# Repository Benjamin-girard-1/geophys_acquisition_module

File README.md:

# Geophysical Acquisition Module

Hardware, embedded firmware, protocol, and host-side software for a modular
geophysical data-acquisition system.

Version 2 uses an ESP32-S3 DevKit as its immutable compute platform and a custom
carrier PCB organized by hardware revision. The current hardware design includes
an AD7779 ADC, an LSM6DSV IMU, MAX-M10S GNSS, SD storage shared with a USB2641,
74HC/HCT595 GPIO expansion, and removable analog acquisition cards.

## Current status

The Version 2 firmware builds with ESP-IDF 5.5. Board safe-state and power
control, portable GPIO/SPI/UART, calibrated analog-input, and ROM-backed CRC
mechanisms, the 74HC/HCT595 driver, bounded analog-card ID measurement, and the
AD7779 register, lifecycle, channel/gain, fixed output-rate, signed sample
decoding, and conversion-frame validation foundations are implemented.
The acquisition task, SD recording owner, and recording controller now provide
the first end-to-end recording implementation and UART live-stream path, while
the remaining protocol inventory is still in progress. Hardware verification
is being completed incrementally.
The authoritative protocol defines fixed 64-byte command messages and portable
512-byte ADC data blocks shared by live capture and SD recording. Fixed command
framing, incremental stream recovery, CRC validation, and the
`HELLO`/`DEVICE_INFO` plus `DEVICE_GET_CONFIG`/`DEVICE_SET_CONFIG` UART slices
are implemented and verified on Rev-1 hardware. Live start/stop, complete
512-byte UART data delivery, the five SD-recording commands,
the portable `\DAT` encoder/decoder, fixed recording-buffer pool, and FatFs
writer are implemented; a clean Rev-1 build mounts and catalogs the SD card,
and now creates, syncs, closes, catalogs, and deletes ADC data files on Rev-1
hardware. A temporary test-only `0xf000` command can read closed recording
files in 38-byte UART chunks; it is implemented in the firmware and host codec
and was used to retrieve and CRC-validate a stored 512-byte block. A two-second
protocol probe produced and cleanly closed 404 fixed
512-byte records while configuration commands remained responsive. The probe
also exposed and led to correction of acquisition-task starvation and a
FreeRTOS queue-set accounting error that rebooted the device after several SD
records. Comparison with the working V1 driver identified and corrected
premature post-reset polling failure, missing reference-output power, missing
SPI software reset, and missing filter synchronization. The earlier all-zero
ADC response was a bench power issue: the main +5 V supply was absent, so 3V3A
was unavailable. Restoring +5 V allowed AD7779 initialization and recording to
proceed. The two expendable recordings that filled the card were enumerated
and deleted through the recording protocol, leaving an empty catalog. A
subsequent fresh probe recorded, downloaded, validated, and deleted ten
512-byte records. All record framing and CRCs passed. That early capture
contained 80 startup conversions near the AD7779 reset rate followed by a
sequence gap. The cause was an ESP-IDF side effect that enabled the DRDY pin
while its handler was attached, before ADC synchronization and SRC settling
completed. The platform attach operation now restores the pin to disabled and
the application enables it explicitly after `ad7779_start()`. A fresh 1 kSPS
probe then produced 25 status-OK records with no missing conversions. The
acquisition hot path now reserves SPI2 and its DMA resources once and launches
one hardware-CS-framed, prepared 32-byte transfer for each DRDY event. A
dedicated core-1 capture task advances the two-buffer DMA pipeline and
copies completed frames into a 256-frame ring; CRC validation, DAT construction,
and storage handoff run independently on core 0. The hardware-tested storage
baseline used two 2 MiB PSRAM buffers: acquisition filled one continuously
while the storage task wrote the other through a 32 KiB internal SDMMC staging
window. A 50-second four-channel 8 kSPS probe crossed both 2 MiB boundaries
without stopping acquisition or losing a conversion. The current
noise-diagnostic implementation expands this to three 2 MiB buffers. Two
buffers accumulate one conversion-count-scheduled batch, while the third keeps
acquisition running during the grouped SD write and single filesystem sync.
Stored-record CRC generation is also deferred to that same SD activity window,
removing the 508-byte PSRAM reread from each 40-conversion record boundary;
live-stream records continue to receive their CRC immediately.
For four channels, batches occur every five minutes at 1 kSPS, two minutes at
2 kSPS, one minute at 4 kSPS, and 30 seconds at 8 kSPS. A Rev-1 8 kSPS test
recorded 35,333 records, crossed five scheduled 6,000-record boundaries with
status-OK and sequence-contiguous records on both sides, and cleanly flushed
the final partial batch. Magnetic-noise comparison remains open. The four-bit
SDMMC bus runs at its verified 40 MHz
high-speed setting; every scheduled batch and the recording close are
synchronized to the filesystem. The SD volume uses FAT32
with 32 KiB clusters so FatFs can issue 32 KiB multi-sector writes instead of
splitting at the former 4 KiB cluster boundaries. A two-second
channels-0–3 probe at 16 kSPS retained all 32,840 consecutive conversions at
625 x 100 ns spacing, with zero sequence gaps and an effective 16,000.04
conversions/s. DAT production waits for eight consecutive ADC frames to pass
CRC; the final short 16 kSPS probe and one-second 1 kSPS control contained only
status-OK records with zero missing conversions. A later 237-second capture retained
every conversion but exposed 72 isolated CRC-marked frame-phase errors at the
fixed 20 MHz SPI clock. Because AD7779 SDO output-valid timing does not support
that read rate in the worst case, lower clocks were tested. Fixed 8 MHz was
clean at 1 kSPS but could not complete valid frames at 16 kSPS with the current
DRDY-to-DMA launch latency. Fixed 10 MHz and 12 MHz produced records but still
lost conversions. A longer fixed-16-MHz capture then lost 23,438 conversions
and contained 243 CRC-marked frame errors in 93.9 seconds. The current
diagnostic build returned to fixed 20 MHz and lets the SPI peripheral assert
and release CS around every DMA burst. A two-second channels-0–3 16 kSPS probe
retained all 32,480 conversions with zero gaps, but two isolated phase errors
remained. Per-frame CS is therefore fast enough but does not by itself correct
the 20 MHz SDO integrity failure.
Configuration currently applies the stopped-device ADC rate, channel mask,
per-channel gains, and three sequenced acquisition rails; +5 VA and IMU remain
status-only. The +18 V rail is owned by a dedicated stopped-acquisition
magnetic SET/RESET command that returns the rail and pulse outputs to their
safe state. The Python host now has streaming
start/stop codecs, an incremental mixed command/data parser, named-reply
matching during live data, byte-exact validated capture, continuity counters,
and a desktop GUI with manual USB/COM selection, recording management, and a
separate live-plot tab. Its Config tab now reads device status and applies the
stopped-device ADC rate, four-channel slot selection, per-channel gains, and
acquisition-rail requests.
It also separates device-reported power-rail states from editable manual rail
requests and provides a detected-card-gated SET/RESET pulse control.
The GUI connection and recording catalog were exercised against Rev-1,
including creation, stop/close, catalog, and deletion of a GUI test recording.
A reversible channels-0–3 configuration update also passed on Rev-1. Firmware
live delivery was then exercised at 921600 baud with eight channels at 1 kSPS
and with four-channel decimation-by-5: start/stop replies and all received block
CRCs passed, streaming continued while an SD recording was opened, and
reconnect succeeded after the five-second session timeout. The live blocks
still expose the known ADC critical status and startup sequence loss, so
scientific-data validation remains open.

On 2026-09-29, the currently inserted SD card mounted and its six-file catalog
remained readable, but a new recording faulted on its first 512-byte write.
The failure reproduced with the untouched default `0xFF` configuration and
with channels 0–3 (`0x0F`), including after a device reset, while an `0x0F`
live stream continued to deliver validly framed blocks. Querying the retained
recording failure through `RECORDING_STOP` returned `0x0a` (`storage full`).
This isolates the failure from host configuration and four-channel
acquisition; space must be freed or the FAT32 volume repaired before recording.

The first Bluetooth Low Energy slice is also implemented. When enabled, the
ESP32-S3 advertises `Geophys Acquisition`, accepts one BLE central, and answers
`HELLO` with the existing `DEVICE_INFO` message. The desktop host can scan,
connect, and display that identity; other commands and live data remain
disabled on Bluetooth for now. Rev-1 bench verification passed BLE discovery
and `HELLO` while a USB command session remained active. The current
2026-10-03 field-test build intentionally sets `APP_BLUETOOTH_ENABLED` to zero
in `version_2/firmware/app/app.c`. This radio-silent diagnostic configuration
removed the measured 60–70 ms BLE advertising disturbance and preserves the
implemented BLE code for later re-enablement.

The same field-test build enables unattended SD recording. With no valid saved
configuration, its defaults are 8 kSPS, channels 0–3 enabled, gain x8 on
channels 0–2, and gain x1 on channel 3; channels 4–7 are disabled. A successful
wired `DEVICE_SET_CONFIG` commits the sample rate, channel mask, and all eight
gains to the ESP32's wear-levelled internal flash. These settings are restored
after reset or power loss; live rail/status fields are not persistent. The
firmware waits five seconds after application initialization, then creates the
first free name from `field000` through `field254` and starts acquisition with
the restored settings. Holding the ESP32-S3 DevKitC BOOT button for three
seconds stops the ADC, drains the PSRAM buffers, syncs the file, and closes it.
A hard power-off cannot run that cleanup: after holding BOOT, wait for the
close to finish before switching the battery off. The RESET button remains an
immediate reset and must not be used to stop a recording.

New SD recordings reserve a self-contained 32 KiB header region. Its first
4096 bytes are printable JSON containing the recording name, device and
firmware/hardware identity, card types, channel mask, gain for every channel,
sample rate, power state, channel mapping, and a link to the project tools.
The rest reserves 896 fixed 32-byte UTC/orientation checkpoints; they are
currently zero placeholders because GNSS is not installed and the IMU path is
not yet implemented. ADC DAT blocks begin at byte 32768. The JSON descriptor
passed native/Python tests and a Rev-1 readback after the 2026-10-07 flash:
`field023` had a CRC-valid, printable JSON descriptor with the configured
per-channel gains and a CRC-valid first `\DAT` block at byte 32768. The firmware
now keeps unattended recording stopped after a wired `RECORDING_STOP`, matching
the BOOT-button stop behavior. A short `field025` check confirmed that the board
stayed idle and the closed file could be read. Long-duration timing verification
remains open.

The complete wire contract is
[shared/protocol/protocol.md](shared/protocol/protocol.md). It is the sole
authority for framing, identifiers, results, command payloads, and ADC data
blocks.

See [ARCHITECTURE.md](ARCHITECTURE.md) for module responsibilities, dependency
rules, initialization order, and the detailed implementation-status table.
Milestone-1 execution and verification are tracked in
[version_2/docs/firmware_implementation_checklist.md](version_2/docs/firmware_implementation_checklist.md).

## Repository layout

```text
.
├── ARCHITECTURE.md              Firmware architecture and dependency rules
├── shared/
│   ├── kicad-libraries/         Shared KiCad symbols and footprints
│   ├── protocol/                Firmware/host wire-protocol specification
│   ├── third_party/             Pinned external dependencies
│   └── tools/                   Repository-wide development utilities
├── version_1/                   Earlier product generation
└── version_2/
    ├── docs/                    Datasheets and documentation
    ├── firmware/
    │   ├── common/              Portable types shared across firmware layers
    │   ├── main/                ESP-IDF entry point and composition root
    │   ├── app/                 Product behavior and FreeRTOS tasks
    │   ├── boards/              Custom carrier-board integration by revision
    │   ├── analog_cards/        Removable analog-card integration
    │   ├── drivers/             Portable component-specific drivers
    │   ├── data_format/         Portable serialized acquisition records
    │   ├── protocol/            Firmware framing and message encoding
    │   ├── transports/          UART, USB, and future byte transports
    │   ├── platform/
    │   │   └── esp32s3_devkit/  Immutable DevKit and ESP-IDF integration
    │   └── cmake/               Shared build helpers when required
    ├── hardware/
    │   ├── pcb/                 KiCad projects organized by revision
    │   └── mechanical/          Mechanical design files
    └── software/
        ├── apps/                Host and recording diagnostics
        └── packages/recording/  Shared Python recording decoder
```

## Firmware boundaries

- `common/` defines dependency-free status categories and other truly
  cross-layer portable types.
- `main/` initializes the platform, selected board, and application.
- `app/` owns acquisition, processing, storage, communication, and product state.
- `boards/` maps the custom PCB wiring to portable drivers and platform services, including the
  Rev-1 mainboard's 18 V rail and physical shift-register outputs.
- `analog_cards/` describes complete removable card assemblies. Magnetic SET/RESET pulse generation
  belongs in `analog_cards/magnetic/` and is not shared with `analog_cards/acc_geoph/`.
- `drivers/` implements individual components without depending on ESP-IDF,
  FreeRTOS, or board wiring.
- `data_format/` defines transport- and storage-independent acquisition-record
  serialization.
- `platform/esp32s3_devkit/` isolates ESP-IDF and immutable DevKit details.
- `protocol/` implements transport-independent framing and messages.
- `transports/` move bytes without interpreting application commands.
- `shared/protocol/` defines the wire contract used by firmware and host tools.

## Version 2 firmware components

The current scaffolds cover:

- AD7779 eight-channel ADC
- LSM6DSV accelerometer and gyroscope
- MAX-M10S GNSS receiver
- 74HC/HCT595 shift register
- Magnetic analog acquisition card
- Geophysical accelerometer card
- Analog-card detection
- Acquisition, processing, storage, communication, and Bluetooth tasks
- UART and USB transports
- Transport-independent protocol framing and messages
- Portable 512-byte ADC-record format

## Building

Activate an ESP-IDF 5.5 environment, then build from `version_2/firmware/`:

```sh
cd version_2/firmware
idf.py build
idf.py flash monitor
```

Run `idf.py set-target esp32s3` first only when creating a fresh local build
configuration or changing targets.

An existing local `sdkconfig` created before BLE support will not automatically
pick up the new Bluetooth defaults. Back it up once and regenerate it before
the first BLE-enabled build:

```sh
mv sdkconfig sdkconfig.pre-ble
idf.py set-target esp32s3
```

Generated `build/`, `sdkconfig`, managed components, binaries, KiCad local state,
editor files, and locally stored vendor datasheet PDFs are excluded by the root
`.gitignore`. Datasheet source links remain tracked in
`version_2/docs/datasheet.txt`.

## Development guidance

Before adding a module or function, consult the “Where new code belongs” table
in [ARCHITECTURE.md](ARCHITECTURE.md#where-new-code-belongs). Keep component
drivers portable, keep physical Rev-1 wiring in `boards/rev_1`, and keep protocol
encoding independent of UART, USB, or Bluetooth.

Update the architecture implementation-status table when an interface becomes
usable, an implementation passes its software tests, or functionality is
verified on hardware.

## Plotting an extracted recording

The small developer tool opens a file chooser in the sibling
`geophys_experiments/` directory, then validates and plots the selected
recording:

```sh
python3 version_2/software/apps/dev_tools/launch_plot.py
```

Pass a path as the first argument to plot a different recording. The application
reads the binary file without modifying it and displays raw ADC counts.

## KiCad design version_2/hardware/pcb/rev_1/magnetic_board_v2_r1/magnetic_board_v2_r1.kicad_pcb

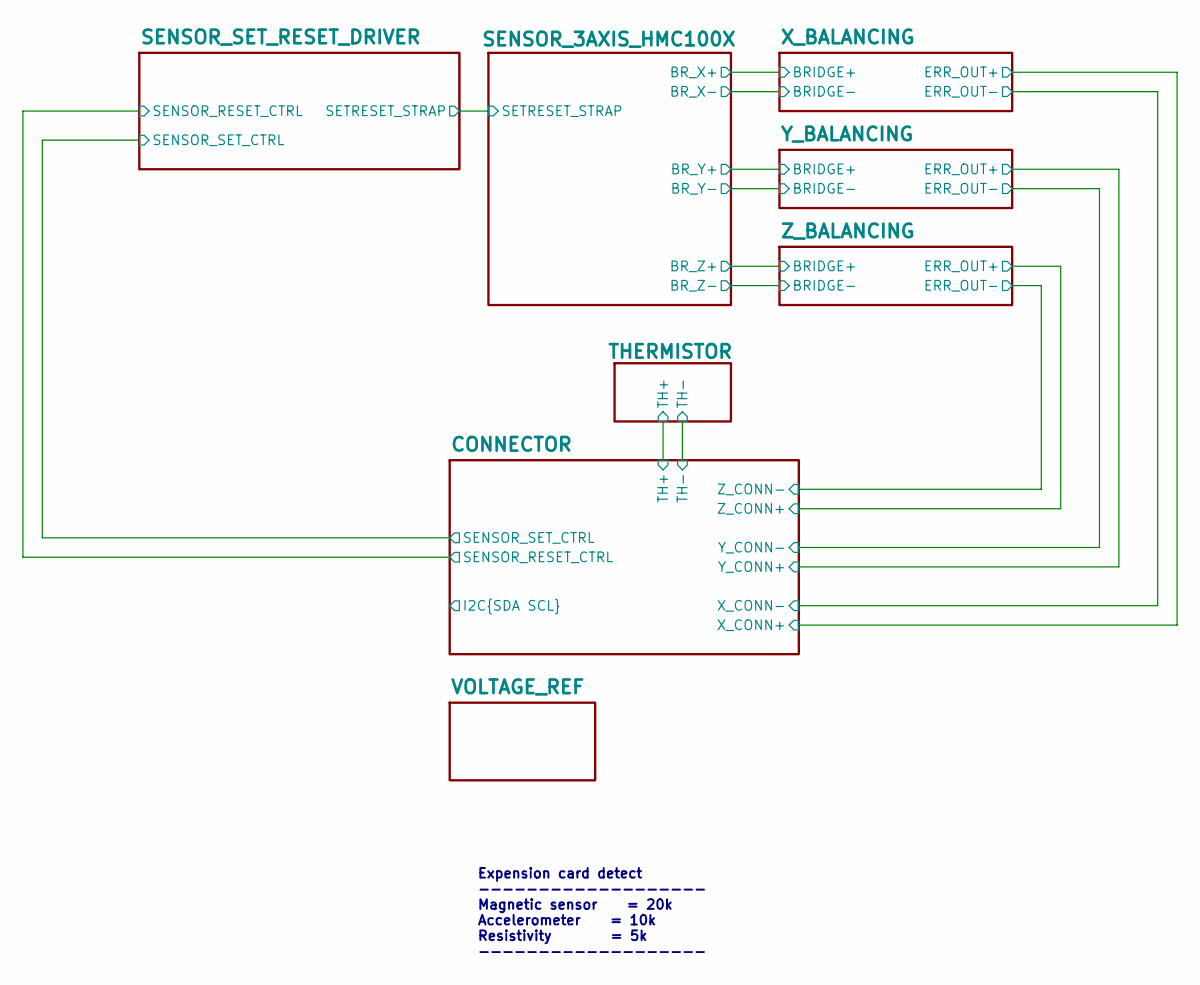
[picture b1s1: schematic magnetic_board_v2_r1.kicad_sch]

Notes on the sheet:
Expension card detect ------------------- Magnetic sensor = 20k Accelerometer = 10k Resistivity = 5k -------------------

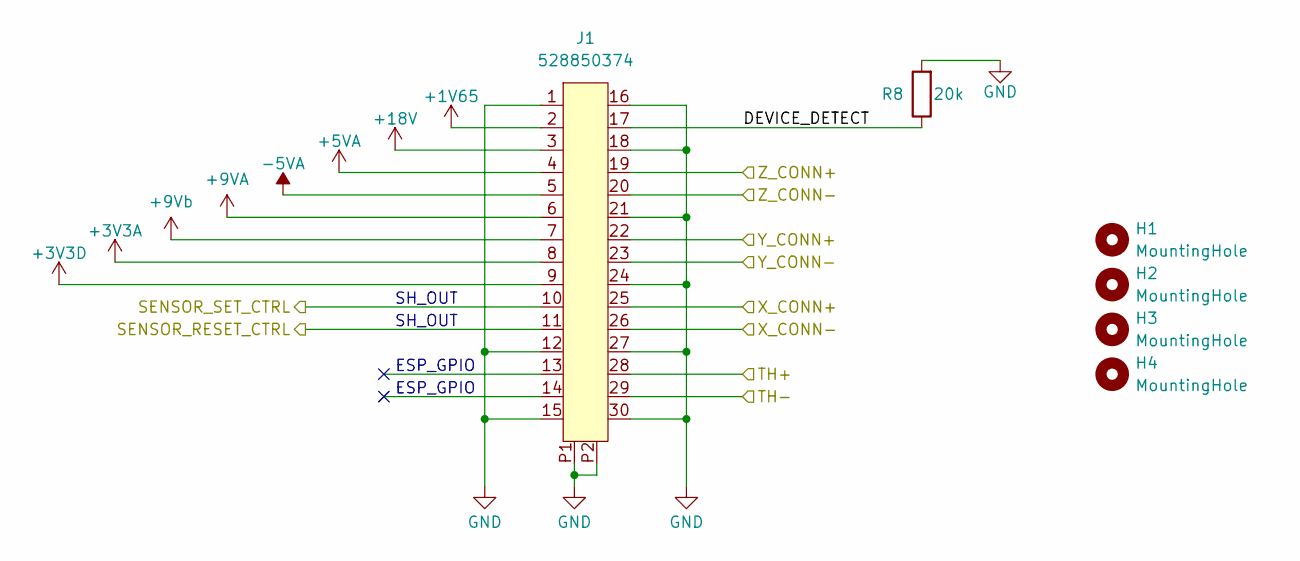
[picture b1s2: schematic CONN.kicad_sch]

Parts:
H1, H2, H3, H4: MountingHole; MountingHole_4.3mm_M4
J1: 528850374; CON_528850374_MOL
R8: 20k; R_0603_1608Metric; LCSC C2076520

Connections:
+1V65: J1.2; also elsewhere on the board
+3V3A: J1.8; also elsewhere on the board
+3V3D: J1.9
+5VA: J1.4
+9VA: J1.6; also elsewhere on the board
+9Vb: J1.7; also elsewhere on the board
+18V: J1.3; also elsewhere on the board
-5VA: J1.5
/CONNECTOR/DEVICE_DETECT: J1.17, R8.1
/CONNECTOR/SENSOR_RESET_CTRL: J1.11; also elsewhere on the board
/CONNECTOR/SENSOR_SET_CTRL: J1.10; also elsewhere on the board
/CONNECTOR/TH+: J1.28; also elsewhere on the board
/CONNECTOR/TH-: J1.29; also elsewhere on the board
/CONNECTOR/X_CONN+: J1.25; also elsewhere on the board
/CONNECTOR/X_CONN-: J1.26; also elsewhere on the board
/CONNECTOR/Y_CONN+: J1.22; also elsewhere on the board
/CONNECTOR/Y_CONN-: J1.23; also elsewhere on the board
/CONNECTOR/Z_CONN+: J1.19; also elsewhere on the board
/CONNECTOR/Z_CONN-: J1.20; also elsewhere on the board
GND: J1.1, J1.12, J1.15, J1.16, J1.18, J1.21, J1.24, J1.27, J1.30, J1.P1, J1.P2, R8.2; also elsewhere on the board

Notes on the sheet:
ESP_GPIO
SH_OUT

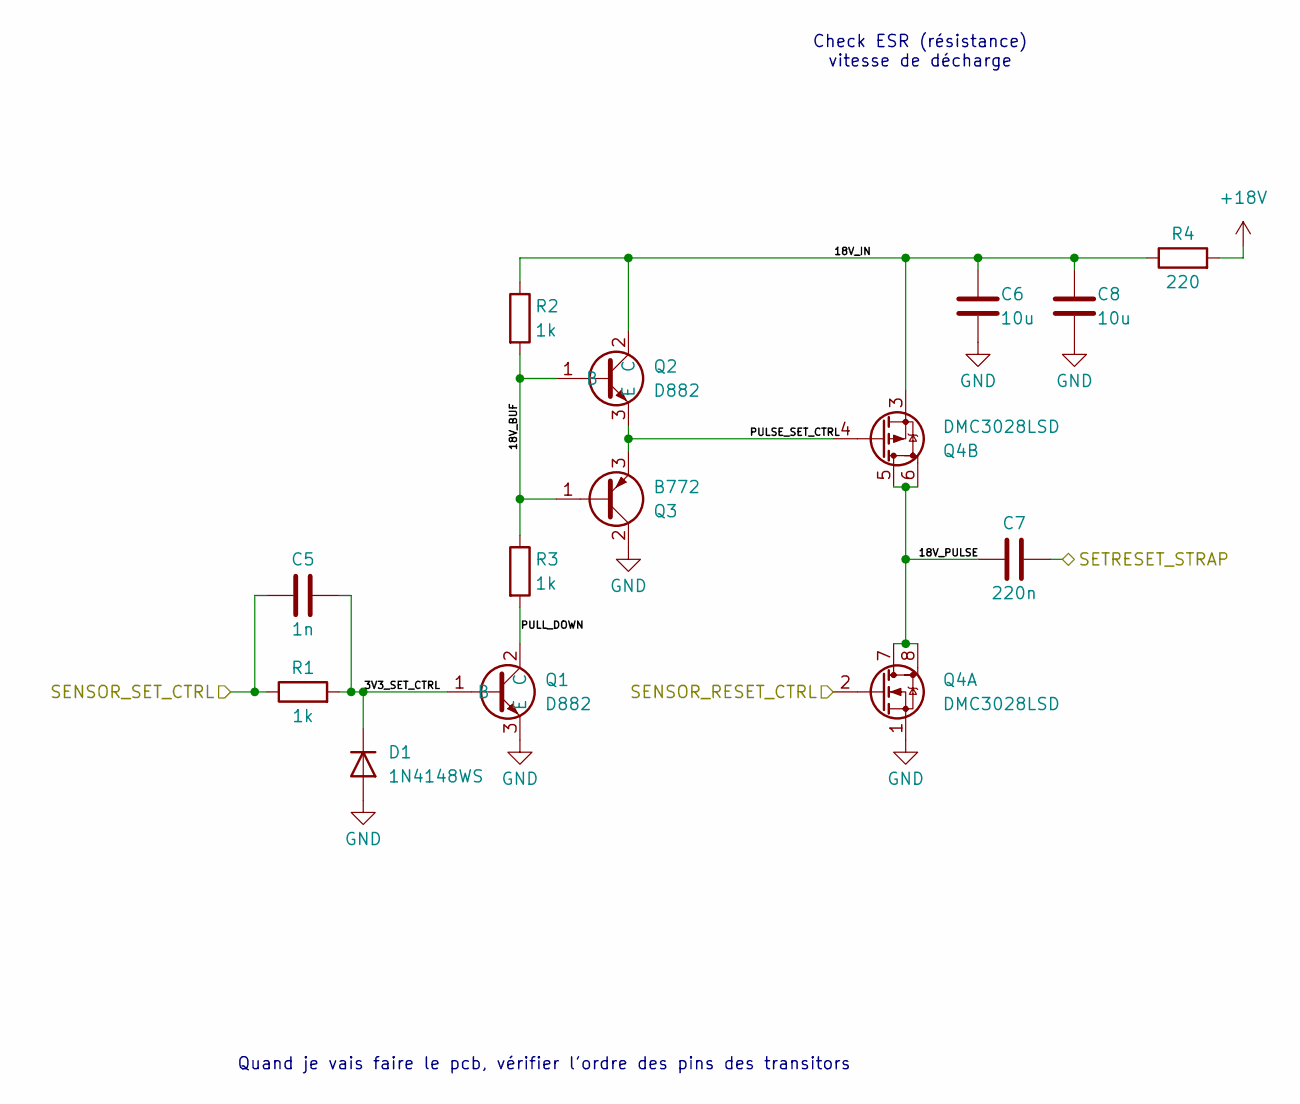
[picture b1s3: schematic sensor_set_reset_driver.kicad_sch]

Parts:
C5: 1n; C_0603_1608Metric; LCSC C1588
C6, C8: 10u; C_1206_3216Metric; LCSC C13585
C7: 220n; C_0805_2012Metric; LCSC C5378
D1: 1N4148WS; D_SOD-323; LCSC C2128
Q1, Q2: D882; SOT-89-3; LCSC C9634
Q3: B772; SOT-89-3; LCSC C24278
Q4: DMC3028LSD; SO-8_3.9x4.9mm_P1.27mm; LCSC C460874
R1, R2, R3: 1k; R_0603_1608Metric; LCSC C21190
R4: 220; R_2512_6332Metric; LCSC C4202072

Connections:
+18V: R4.2; also elsewhere on the board
/CONNECTOR/SENSOR_RESET_CTRL: Q4.2 (G1); also elsewhere on the board
/CONNECTOR/SENSOR_SET_CTRL: C5.1, R1.1; also elsewhere on the board
/SENSOR_3AXIS_HMC100X/SETRESET_STRAP: C7.2; also elsewhere on the board
/SENSOR_SET_RESET_DRIVER/3V3_SET_CTRL: C5.2, D1.1 (K), Q1.1 (B), R1.2
/SENSOR_SET_RESET_DRIVER/18V_BUF: Q2.1 (B), Q3.1, R2.2, R3.1
/SENSOR_SET_RESET_DRIVER/18V_IN: C6.1, C8.1, Q2.2 (C), Q4.3 (S2), R2.1, R4.1
/SENSOR_SET_RESET_DRIVER/18V_PULSE: C7.1, Q4.5 (D2), Q4.6 (D2), Q4.7 (D1), Q4.8 (D1)
/SENSOR_SET_RESET_DRIVER/PULL_DOWN: Q1.2 (C), R3.2
/SENSOR_SET_RESET_DRIVER/PULSE_SET_CTRL: Q2.3 (E), Q3.3, Q4.4 (G2)
GND: C6.2, C8.2, D1.2 (A), Q1.3 (E), Q3.2, Q4.1 (S1); also elsewhere on the board

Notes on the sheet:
Check ESR (résistance) vitesse de décharge
Quand je vais faire le pcb, vérifier l'ordre des pins des transitors

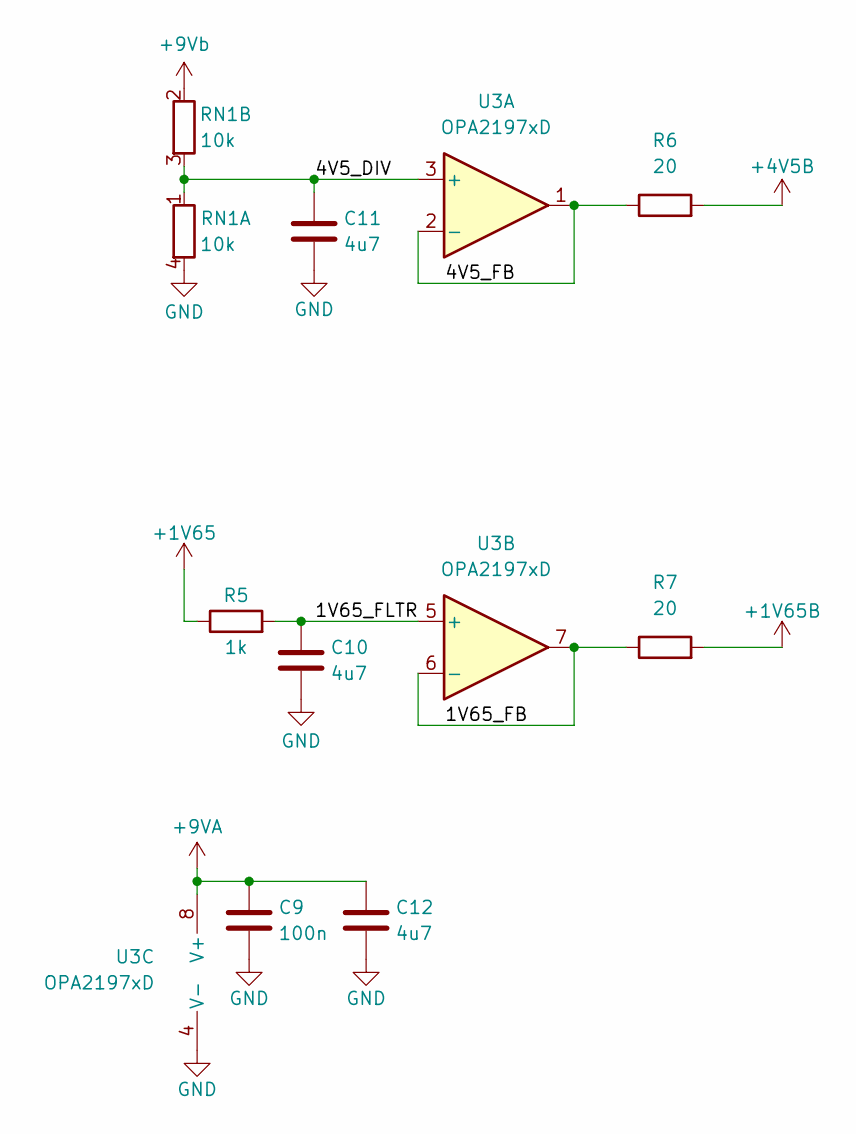
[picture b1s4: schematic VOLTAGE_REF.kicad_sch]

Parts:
C9: 100n; C_0603_1608Metric; LCSC C14663
C10, C11, C12: 4u7; C_1206_3216Metric; LCSC C29823
R5: 1k; R_0603_1608Metric; LCSC C21190
R6, R7: 20; R_0603_1608Metric; LCSC C22950
RN1: 10k; R_Array_Convex_2x0603; LCSC C2654064
U3: OPA2197xD; SOIC-8_3.9x4.9mm_P1.27mm; LCSC C139363

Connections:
+1V65: R5.1; also elsewhere on the board
+1V65B: R7.2; also elsewhere on the board
+4V5B: R6.2; also elsewhere on the board
+9VA: C9.1, C12.1, U3.8 (V+); also elsewhere on the board
+9Vb: RN1.2 (R2.1); also elsewhere on the board
/VOLTAGE_REF/1V65_FB: R7.1, U3.6 (-), U3.7
/VOLTAGE_REF/1V65_FLTR: C10.1, R5.2, U3.5 (+)
/VOLTAGE_REF/4V5_DIV: C11.1, RN1.1 (R1.1), RN1.3 (R2.2), U3.3 (+)
/VOLTAGE_REF/4V5_FB: R6.1, U3.1, U3.2 (-)
GND: C9.2, C10.2, C11.2, C12.2, RN1.4 (R1.2), U3.4 (V-); also elsewhere on the board

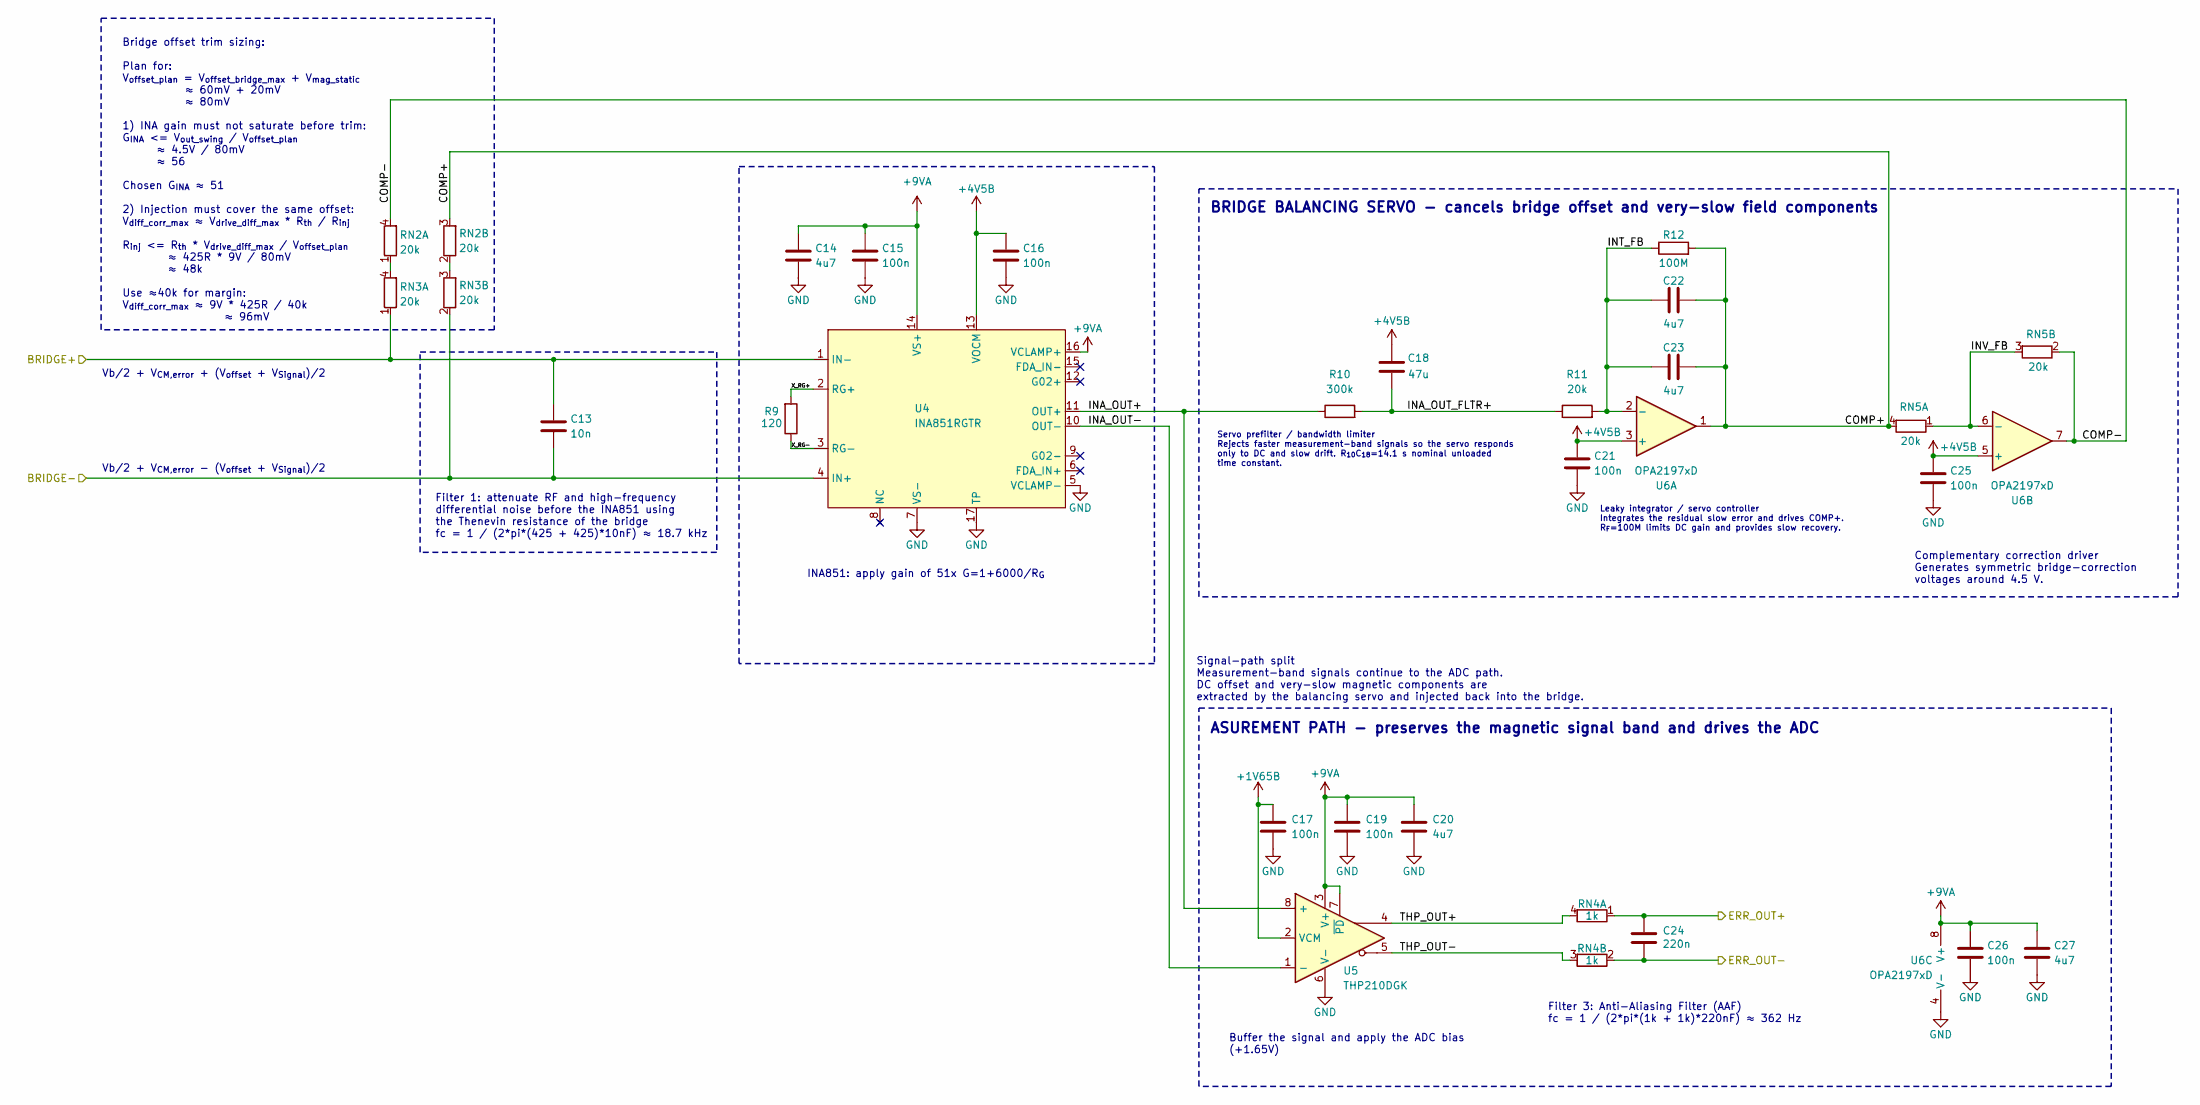
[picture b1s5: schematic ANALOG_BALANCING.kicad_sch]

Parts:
C13: 10n; C_0603_1608Metric; LCSC C57112
C14, C20, C22, C23, C27: 4u7; C_1206_3216Metric; LCSC C29823
C15, C16, C17, C19, C21, C25, C26: 100n; C_0603_1608Metric; LCSC C14663
C18: 47u; C_1206_3216Metric; LCSC C96123
C24: 220n; C_0805_2012Metric; LCSC C5378
R9: 120; R_0603_1608Metric; LCSC C860088
R10: 300k; R_0603_1608Metric; LCSC C5948140
R11: 20k; R_0603_1608Metric; LCSC C2076520
R12: 100M; R_0805_2012Metric; LCSC C169373
RN2, RN3, RN5: 20k; R_Array_Convex_2x0603; LCSC C5553154
RN4: 1k; R_Array_Convex_2x0603; LCSC C1731140
U4: INA851RGTR; VQFN-16-1EP_3x3mm_P0.5mm_EP1.68x1.68mm; LCSC C5371575
U5: THP210DGK; VSSOP-8_3x3mm_P0.65mm; LCSC C976185
U6: OPA2197xD; SOIC-8_3.9x4.9mm_P1.27mm; LCSC C139363

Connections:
+1V65B: C17.1, U5.2 (VCM); also elsewhere on the board
+4V5B: C16.1, C18.2, C21.1, C25.1, U4.13 (VOCM), U6.3 (+), U6.5 (+); also elsewhere on the board
+9VA: C14.1, C15.1, C19.1, C20.1, C26.1, C27.1, U4.14 (VS+), U4.16 (VCLAMP+), U5.3 (V+), U5.7 (~PD), U6.8 (V+); also elsewhere on the board
/CONNECTOR/X_CONN+: C24.2, RN4.1 (R1.1); also elsewhere on the board
/CONNECTOR/X_CONN-: C24.1, RN4.2 (R2.1); also elsewhere on the board
/SENSOR_3AXIS_HMC100X/BR_X+: C13.1, RN3.1 (R1.1), U4.1 (IN-); also elsewhere on the board
/SENSOR_3AXIS_HMC100X/BR_X-: C13.2, RN3.2 (R2.1), U4.4 (IN+); also elsewhere on the board
/X_BALANCING/COMP+: C22.2, C23.2, R12.2, RN2.3 (R2.2), RN5.4 (R1.2), U6.1
/X_BALANCING/COMP-: RN2.4 (R1.2), RN5.2 (R2.1), U6.7
/X_BALANCING/INA_OUT+: R10.1, U4.11 (OUT+), U5.8 (+)
/X_BALANCING/INA_OUT-: U4.10 (OUT-), U5.1 (-)
/X_BALANCING/INA_OUT_FLTR+: C18.1, R10.2, R11.1
/X_BALANCING/INT_FB: C22.1, C23.1, R11.2, R12.1, U6.2 (-)
/X_BALANCING/INV_FB: RN5.1 (R1.1), RN5.3 (R2.2), U6.6 (-)
/X_BALANCING/THP_OUT+: RN4.4 (R1.2), U5.4
/X_BALANCING/THP_OUT-: RN4.3 (R2.2), U5.5
/X_BALANCING/X_RG+: R9.2, U4.2 (RG+)
/X_BALANCING/X_RG-: R9.1, U4.3 (RG-)
GND: C14.2, C15.2, C16.2, C17.2, C19.2, C20.2, C21.2, C25.2, C26.2, C27.2, U4.5 (VCLAMP-), U4.7 (VS-), U4.17 (TP), U5.6 (V-), U6.4 (V-); also elsewhere on the board
unnamed: RN2.1 (R1.1), RN3.4 (R1.2)
unnamed: RN2.2 (R2.1), RN3.3 (R2.2)

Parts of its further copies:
C28, C43: 10n; C_0603_1608Metric; LCSC C57112
C29, C35, C37, C38, C42, C44, C50, C52, C53, C57: 4u7; C_1206_3216Metric; LCSC C29823
C30, C31, C32, C34, C36, C40, C41, C45, C46, C47, C49, C51, C55, C56: 100n; C_0603_1608Metric; LCSC C14663
C33, C48: 47u; C_1206_3216Metric; LCSC C96123
C39, C54: 220n; C_0805_2012Metric; LCSC C5378
R13, R17: 120; R_0603_1608Metric; LCSC C860088
R14, R18: 300k; R_0603_1608Metric; LCSC C5948140
R15, R19: 20k; R_0603_1608Metric; LCSC C2076520
R16, R20: 100M; R_0805_2012Metric; LCSC C169373
RN6, RN7, RN9, RN10, RN11, RN13: 20k; R_Array_Convex_2x0603; LCSC C5553154
RN8, RN12: 1k; R_Array_Convex_2x0603; LCSC C1731140
U7, U10: INA851RGTR; VQFN-16-1EP_3x3mm_P0.5mm_EP1.68x1.68mm; LCSC C5371575
U8, U11: THP210DGK; VSSOP-8_3x3mm_P0.65mm; LCSC C976185
U9, U12: OPA2197xD; SOIC-8_3.9x4.9mm_P1.27mm; LCSC C139363

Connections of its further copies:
+1V65B: C32.1, C47.1, U8.2 (VCM), U11.2 (VCM); also elsewhere on the board
+4V5B: C31.1, C33.2, C36.1, C40.1, C46.1, C48.2, C51.1, C55.1, U7.13 (VOCM), U9.3 (+), U9.5 (+), U10.13 (VOCM), U12.3 (+), U12.5 (+); also elsewhere on the board
+9VA: C29.1, C30.1, C34.1, C35.1, C41.1, C42.1, C44.1, C45.1, C49.1, C50.1, C56.1, C57.1, U7.14 (VS+), U7.16 (VCLAMP+), U8.3 (V+), U8.7 (~PD), U9.8 (V+), U10.14 (VS+), U10.16 (VCLAMP+), U11.3 (V+), U11.7 (~PD), U12.8 (V+); also elsewhere on the board
/CONNECTOR/Y_CONN+: C39.2, RN8.1 (R1.1); also elsewhere on the board
/CONNECTOR/Y_CONN-: C39.1, RN8.2 (R2.1); also elsewhere on the board
/CONNECTOR/Z_CONN+: C54.2, RN12.1 (R1.1); also elsewhere on the board
/CONNECTOR/Z_CONN-: C54.1, RN12.2 (R2.1); also elsewhere on the board
/SENSOR_3AXIS_HMC100X/BR_Y+: C28.1, RN7.1 (R1.1), U7.1 (IN-); also elsewhere on the board
/SENSOR_3AXIS_HMC100X/BR_Y-: C28.2, RN7.2 (R2.1), U7.4 (IN+); also elsewhere on the board
/SENSOR_3AXIS_HMC100X/BR_Z+: C43.1, RN11.1 (R1.1), U10.1 (IN-); also elsewhere on the board
/SENSOR_3AXIS_HMC100X/BR_Z-: C43.2, RN11.2 (R2.1), U10.4 (IN+); also elsewhere on the board
/Y_BALANCING/COMP+: C37.2, C38.2, R16.2, RN6.3 (R2.2), RN9.4 (R1.2), U9.1
/Y_BALANCING/COMP-: RN6.4 (R1.2), RN9.2 (R2.1), U9.7
/Y_BALANCING/INA_OUT+: R14.1, U7.11 (OUT+), U8.8 (+)
/Y_BALANCING/INA_OUT-: U7.10 (OUT-), U8.1 (-)
/Y_BALANCING/INA_OUT_FLTR+: C33.1, R14.2, R15.1
/Y_BALANCING/INT_FB: C37.1, C38.1, R15.2, R16.1, U9.2 (-)
/Y_BALANCING/INV_FB: RN9.1 (R1.1), RN9.3 (R2.2), U9.6 (-)
/Y_BALANCING/THP_OUT+: RN8.4 (R1.2), U8.4
/Y_BALANCING/THP_OUT-: RN8.3 (R2.2), U8.5
/Y_BALANCING/X_RG+: R13.2, U7.2 (RG+)
/Y_BALANCING/X_RG-: R13.1, U7.3 (RG-)
/Z_BALANCING/COMP+: C52.2, C53.2, R20.2, RN10.3 (R2.2), RN13.4 (R1.2), U12.1
/Z_BALANCING/COMP-: RN10.4 (R1.2), RN13.2 (R2.1), U12.7
/Z_BALANCING/INA_OUT+: R18.1, U10.11 (OUT+), U11.8 (+)
/Z_BALANCING/INA_OUT-: U10.10 (OUT-), U11.1 (-)
/Z_BALANCING/INA_OUT_FLTR+: C48.1, R18.2, R19.1
/Z_BALANCING/INT_FB: C52.1, C53.1, R19.2, R20.1, U12.2 (-)
/Z_BALANCING/INV_FB: RN13.1 (R1.1), RN13.3 (R2.2), U12.6 (-)
/Z_BALANCING/THP_OUT+: RN12.4 (R1.2), U11.4
/Z_BALANCING/THP_OUT-: RN12.3 (R2.2), U11.5
/Z_BALANCING/X_RG+: R17.2, U10.2 (RG+)
/Z_BALANCING/X_RG-: R17.1, U10.3 (RG-)
GND: C29.2, C30.2, C31.2, C32.2, C34.2, C35.2, C36.2, C40.2, C41.2, C42.2, C44.2, C45.2, C46.2, C47.2, C49.2, C50.2, C51.2, C55.2, C56.2, C57.2, U7.5 (VCLAMP-), U7.7 (VS-), U7.17 (TP), U8.6 (V-), U9.4 (V-), U10.5 (VCLAMP-), U10.7 (VS-), U10.17 (TP), U11.6 (V-), U12.4 (V-); also elsewhere on the board
unnamed: RN6.1 (R1.1), RN7.4 (R1.2)
unnamed: RN6.2 (R2.1), RN7.3 (R2.2)
unnamed: RN10.1 (R1.1), RN11.4 (R1.2)
unnamed: RN10.2 (R2.1), RN11.3 (R2.2)

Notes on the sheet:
BRIDGE BALANCING SERVO - cancels bridge offset and very-slow field components
Filter 1: attenuate RF and high-frequency differential noise before the INA851 using the Thenevin resistance of the bridge fc = 1 / (2*pi*(425 + 425)*10nF) ≈ 18.7 kHz
Servo prefilter / bandwidth limiter Rejects faster measurement-band signals so the servo responds only to DC and slow drift. R_{10}C_{18}=14.1 s nominal unloaded time constant.
Buffer the signal and apply the ADC bias (+1.65V)
Vb/2 + V_{CM,error} + (V_{offset} + V_{Signal})/2
Leaky integrator / servo controller Integrates the residual slow error and drives COMP+. R_{F}=100M limits DC gain and provides slow recovery.
Complementary correction driver Generates symmetric bridge-correction voltages around 4.5 V.
Vb/2 + V_{CM,error} - (V_{offset} + V_{Signal})/2
ASUREMENT PATH - preserves the magnetic signal band and drives the ADC
Bridge offset trim sizing: Plan for: V_{offset_plan} = V_{offset_bridge_max} + V_{mag_static} ≈ 60mV + 20mV ≈ 80mV 1) INA gain must not saturate before trim: G_{INA} <= V_{out_swing} / V_{offset_plan} ≈ 4.5V / 80mV ≈ 56 Chosen G_{INA} ≈ 51 2) Injection must cover the same offset: V_{diff_corr_max} 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
INA851: apply gain of 51x G=1+6000/R_{G}
Signal-path split Measurement-band signals continue to the ADC path. DC offset and very-slow magnetic components are extracted by the balancing servo and injected back into the bridge.
Filter 3: Anti-Aliasing Filter (AAF) fc = 1 / (2*pi*(1k + 1k)*220nF) ≈ 362 Hz

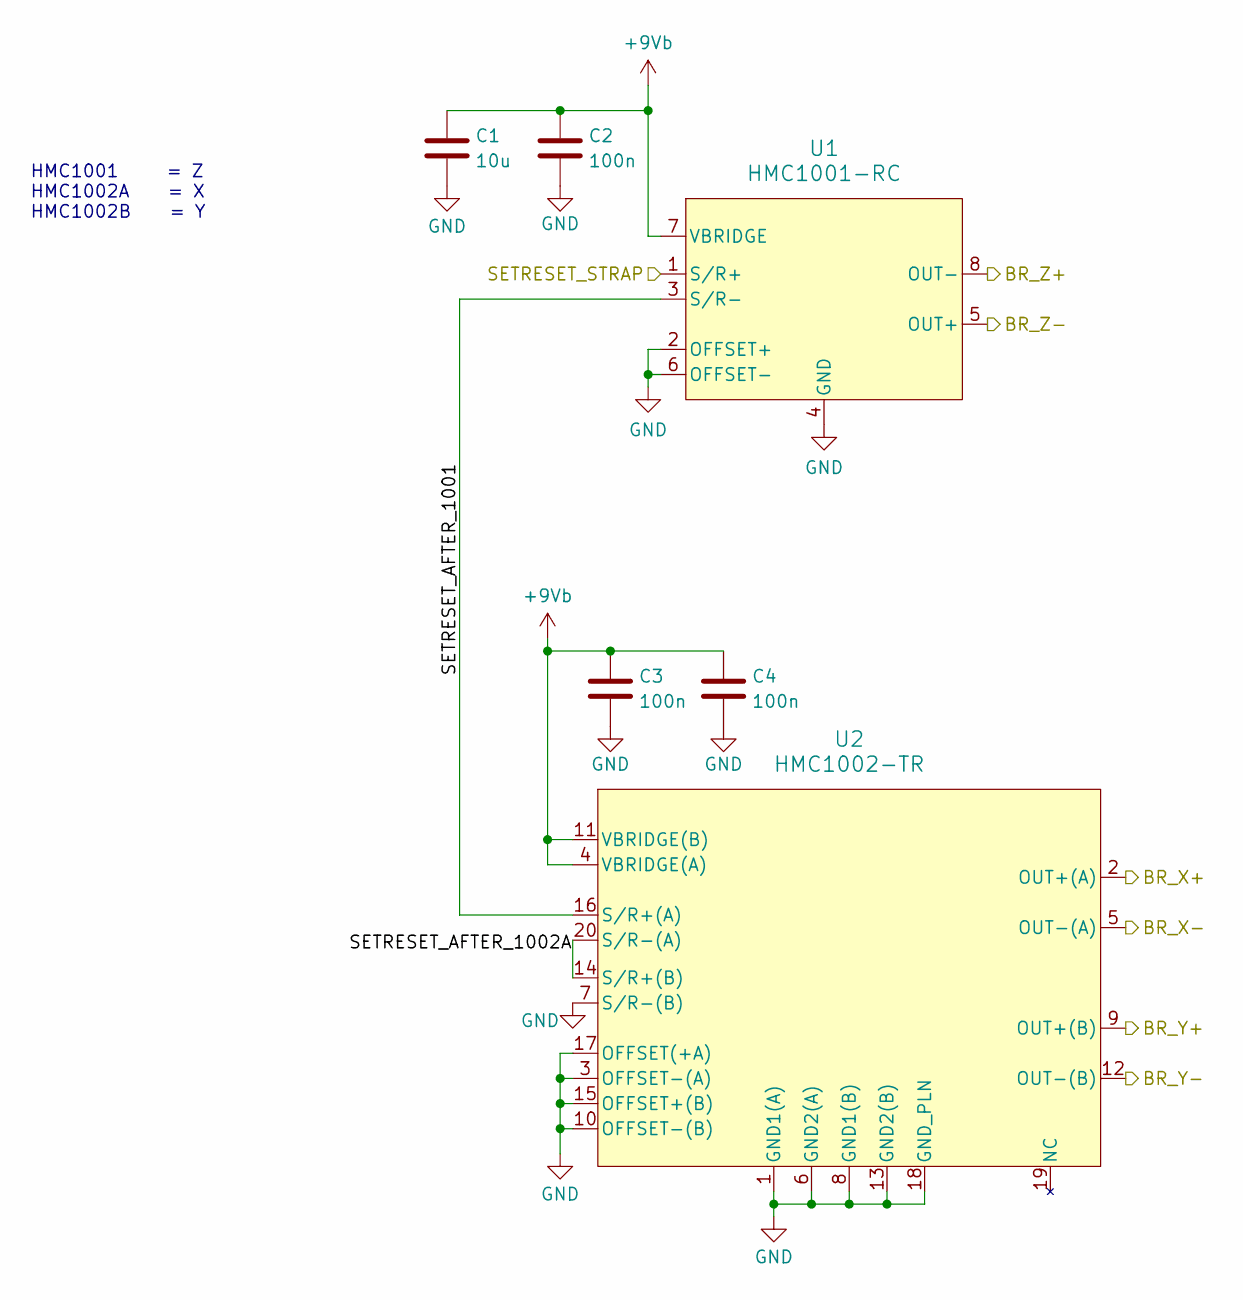
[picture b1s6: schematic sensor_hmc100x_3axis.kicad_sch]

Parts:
C1: 10u; C_1206_3216Metric; LCSC C13585
C2, C3, C4: 100n; C_0603_1608Metric; LCSC C14663
U1: HMC1001-RC; SIP8_HMC1001_HNW
U2: HMC1002-TR; SOIC20_HNW

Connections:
+9Vb: C1.1, C2.1, C3.1, C4.1, U1.7 (VBRIDGE), U2.4 (VBRIDGE(A)), U2.11 (VBRIDGE(B)); also elsewhere on the board
/SENSOR_3AXIS_HMC100X/BR_X+: U2.2 (OUT+(A)); also elsewhere on the board
/SENSOR_3AXIS_HMC100X/BR_X-: U2.5 (OUT-(A)); also elsewhere on the board
/SENSOR_3AXIS_HMC100X/BR_Y+: U2.9 (OUT+(B)); also elsewhere on the board
/SENSOR_3AXIS_HMC100X/BR_Y-: U2.12 (OUT-(B)); also elsewhere on the board
/SENSOR_3AXIS_HMC100X/BR_Z+: U1.8 (OUT-); also elsewhere on the board
/SENSOR_3AXIS_HMC100X/BR_Z-: U1.5 (OUT+); also elsewhere on the board
/SENSOR_3AXIS_HMC100X/SETRESET_AFTER_1001: U1.3 (S/R-), U2.16 (S/R+(A))
/SENSOR_3AXIS_HMC100X/SETRESET_AFTER_1002A: U2.14 (S/R+(B)), U2.20 (S/R-(A))
/SENSOR_3AXIS_HMC100X/SETRESET_STRAP: U1.1 (S/R+); also elsewhere on the board
GND: C1.2, C2.2, C3.2, C4.2, U1.2 (OFFSET+), U1.4 (GND), U1.6 (OFFSET-), U2.1 (GND1(A)), U2.3 (OFFSET-(A)), U2.6 (GND2(A)), U2.7 (S/R-(B)), U2.8 (GND1(B)), U2.10 (OFFSET-(B)), U2.13 (GND2(B)), U2.15 (OFFSET+(B)), U2.17 (OFFSET(+A)), U2.18 (GND_PLN); also elsewhere on the board

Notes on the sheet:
HMC1001 = Z HMC1002A = X HMC1002B = Y

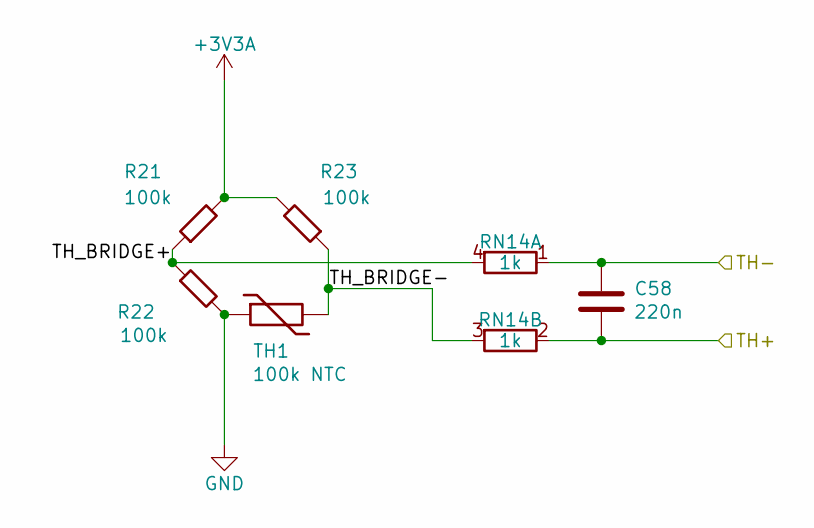
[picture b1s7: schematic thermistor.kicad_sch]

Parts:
C58: 220n; C_0805_2012Metric; LCSC C5378
R21, R22, R23: 100k; R_0603_1608Metric; LCSC C860056
RN14: 1k; R_Array_Convex_2x0603; LCSC C1731140
TH1: 100k NTC; R_0603_1608Metric; LCSC C3154303

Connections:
+3V3A: R21.2, R23.2; also elsewhere on the board
/CONNECTOR/TH+: C58.1, RN14.2 (R2.1); also elsewhere on the board
/CONNECTOR/TH-: C58.2, RN14.1 (R1.1); also elsewhere on the board
/THERMISTOR/TH_BRIDGE+: R21.1, R22.1, RN14.4 (R1.2)
/THERMISTOR/TH_BRIDGE-: R23.1, RN14.3 (R2.2), TH1.2
GND: R22.2, TH1.1; also elsewhere on the board
